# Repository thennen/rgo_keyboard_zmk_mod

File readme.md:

# R-Go split keyboard, converted to fully wireless with nice!nano + ZMK

This is a hardware and firmware mod of the commercially available R-Go split wireless keyboard. The stock electronics are replaced with a [nice!nano v2](https://nicekeyboards.com/nice-nano/) in each half, running [ZMK](https://zmk.dev/) firmware. The result is a truly wireless split, with no cable between the halves and fully programmable keys.

## Why

This replaces my [UltraErgo](https://github.com/thennen/ultraergo), which finally died after a decade or so and is no longer on the market. The R-Go isn't as nice, but it's currently the best low-profile, non-mechanical split keyboard you can buy: thin, compact and comfortable. The stock version has some annoying limitations though:

- **The halves are joined by a hardwired cable**, even on the "wireless" model. Only the connection to the PC is Bluetooth. The cable is also poorly made: a light tug pulls the outer insulation off and exposes the conductors.
- **No real remapping.** The halves of the split spacebar can't be mapped separately, and important keys like Print Screen hide behind Fn.
- **The macro column** on the far left triggers key combinations internally, and a whole key is spent on disabling it.
- **USB is power-only**, so the keyboard can't work over a cable, for example in the BIOS or boot menu.
- **A tiny 230 mAh battery**, even though the case has plenty of room for a bigger one.
- **No tenting.** It's not really "ergo" without it.

ZMK on a nice!nano fixes the electronics side: every key is programmable, both halves are wireless, and USB works for typing and flashing. For tenting, I stuck adhesive tenting stands from AliExpress on the bottom of each half.

## The stock hardware

- **Left half (control board `K900-BT LEFT V1.0`, 2023-06-25):** 100 × 24 × 1 mm with an HS6620 Bluetooth SoC (from HunterSun, now OnMicro), the kind of chip used in cheap smartwatches. Its SDK is only available under NDA, so reflashing the stock board isn't realistic. There's [a datasheet on archive.org](https://archive.org/details/hs6620d-data-sheet-v30/mode/2up) and [some reverse-engineering work](https://github.com/rbaron/HS6620D-smartwatch-reveng).
- **Right half (`K900-RIGHT V1.0`):** a passive board with only connectors, plus the 230 mAh battery (TW 382035). All of the right half's rows and columns, plus battery power, go to the left half over the 20-wire cable.
- **Key matrix:** a membrane with a flat ribbon cable (FFC) in each half. It's 1.0 mm pitch and about 21 mm wide, with a blue stiffener, and plugs into a bottom-contact ZIF connector. The left ribbon uses all 20 pins, the right one 18.

## The mod

Each half gets an adapter PCB with:
- a 20-pin, 1.0 mm FFC connector (TE 2-84952-0) for the stock membrane ribbon
- a nice!nano v2 footprint
- a 2-pin battery header, here for a 600 mAh 502040 LiPo, a big upgrade over the stock 230 mAh

<p align="center"><i>Inside, after the mod: a custom adapter PCB plugs into the stock membrane ribbon, with a nice!nano and its own 600 mAh battery on each side.</i></p>

The KiCad project, Gerbers and ready-to-order zips (`rgo_nicenano_left.zip`, `rgo_nicenano_right.zip`) are in [`rgo_nice!nano/`](rgo_nice!nano/). The PCBs reuse the stock mounting holes, and the inter-half cable is removed entirely.

> **Known PCB mistakes (current revision):**
> - The nice!nano's ground isn't connected to the battery's ground. Add a jumper wire between them.
> - On the right-hand board, the mounting hole is slightly out of place. Filing it a bit makes it fit.

Fitting notes:
- The case's inner space is about 6 mm deep and 21 mm tall in the flat part. The usable length is about 150 mm in the left half and 135 mm in the right half.
- The nice!nano fits inside easily, but it doesn't line up with the stock USB-C cutout because of the angle. The right half has no cutout at all, so expect to cut new openings.
- Socket headers are too tall for the space, even Mill-Max "super low profile" at 4 mm.

### Opening the case

Push a sharp piece of plastic, such as a plastic razor blade, into the seam. Each half has three clips on each flat side and four on the jagged side. Start with the flat sides.

The magnets tend to pop out because the glue is weak. You can glue them back in, but check the polarity so they attract instead of repel.

> **Wired vs. wireless:** The cheaper **wired** R-Go split also works as a base for this mod, since the matrix and ribbon are the same idea. But it has a hidden screw underneath the glued panels, which is quite annoying to get out.

## Firmware

The ZMK config is in [`config/boards/shields/rgo/`](config/boards/shields/rgo/), set up as a split shield (`rgo_left` / `rgo_right`) on `nice_nano_v2`. The left half is the central.

The membrane matrix (8 rows × 12 columns on the left, 8 × 10 on the right) was reverse-engineered with the `reverse_engineer_key_matrix*.py` and `capture_keys.py` scripts. They flash a test keymap that gives every matrix position a unique keycode, then record which key on the board produces which code. The resulting mapping is the `matrix-transform` in `rgo.dtsi`.

Keymap highlights (`rgo.keymap`):
- **Enter on the right half of the spacebar.** This was one of the most important reasons for the mod, since the stock firmware can't remap the two spacebar halves separately.
- **Fn layer:** Bluetooth profiles, bootloader (left: Fn+1, right: the key labeled RCtrl +7), soft-off, media keys, Print Screen, Insert and more.
- **Unicode** via [zmk-unicode](https://github.com/urob/zmk-unicode), using WinCompose.
- **Recorded macros** on the far-left column (see below).

### Recorded macros

The six keys of the far-left macro column are record-and-play slots, stored in the keyboard's flash so they survive reboots and reflashing.

- **Record:** Fn + slot key, type the sequence, then Fn + slot key again to stop and save. Use the right Fn for the top two keys, because the left Fn shares their matrix column. Keys aren't sent to the computer while recording, so the keyboard seems dead until you stop.
- **Play:** slot key alone.
- **Erase:** record an empty sequence (Fn + slot key twice). `settings_reset` also erases them.
- Up to 64 keystrokes per slot.
- Only the left half needs reflashing for changes here, since it does all the recording.

The code is in `recmac/`, a small Zephyr module that `zephyr/module.yml` at the repo root makes the build pick up. Settings like max length and playback speed are in `recmac/Kconfig`.

## Building the firmware

### Easiest: GitHub Actions (no local toolchain needed)

Every push to GitHub builds the firmware in the cloud. Three files drive it:
- `.github/workflows/build.yml` runs ZMK's reusable build workflow, pinned to v0.3.
- `build.yaml` lists which board/shield combos to build: left, right and settings_reset.
- `config/west.yml` sets which ZMK version and modules (zmk-unicode) to build against.

To get firmware:
1. Push, or on GitHub go to the Actions tab, pick the workflow and click "Run workflow".
2. Open the finished run in the Actions tab and download the `firmware` zip at the bottom.
3. Unzip, put a half into bootloader mode, and copy its `.uf2` onto the drive that appears.

To upgrade ZMK later, bump `revision` for both zmk and zmk-unicode in `config/west.yml`, and the `@v0.3` in the workflow. v0.4+ is Zephyr 4.1, where the board becomes `nice_nano//zmk` in `build.yaml`.

### tl;dr: local build and flash when the environment is already set up

Put the keyboard into bootloader mode (left half: Fn-1, right half: RCtrl-7), then in cmd.exe:
```
set PATH=%PATH%;"C:\Users\t\anaconda3\Scripts";"C:\QMK_MSYS\mingw64\bin"
subst Q: "C:\Users\t\Proton Drive\My files\github\rgo_wireless"
cd desktop\zmk\app
west build -d build/left -p -b nice_nano_v2 -- -DSHIELD=rgo_left -DZMK_CONFIG="Q:/config" -DZMK_EXTRA_MODULES="Q:/zmk-unicode;Q:/"
copy build\left\zephyr\zmk.uf2 G:\zmk.uf2
```

### Setting up a local build on Windows

You need to clone zmk. It isn't in this repo because it's 4 GB.

```
pip install west
set PATH=%PATH%;"C:\Users\t\anaconda3\Scripts";"C:\QMK_MSYS\mingw64\bin"

git clone https://github.com/zmkfirmware/zmk zmk
cd zmk
git checkout v0.3
west init -l app/
west update
west zephyr-export
```

From elevated powershell:
```
choco install cmake ninja dtc-msys2 gperf
```

```
pip install -r zephyr/scripts/requirements-base.txt
```

```
cd %HOMEPATH%
wget https://github.com/zephyrproject-rtos/sdk-ng/releases/download/v0.16.3/zephyr-sdk-0.16.3_windows-x86_64.7z
7z x zephyr-sdk-0.16.3_windows-x86_64.7z
cd zephyr-sdk-0.16.3
setup.cmd
```

To build, you need to be in the zmk/app folder:
```
cd desktop\zmk\app
```

The build command has to point to this repo's config directory, but west can't handle spaces in paths, even quoted. I use subst as a workaround on Windows:

```
subst Q: "C:\Users\t\Proton Drive\My files\github\rgo_wireless"
```

For a split build:
```
west build -d build/left -p -b nice_nano_v2 -- -DSHIELD=rgo_left -DZMK_CONFIG="Q:/config" -DZMK_EXTRA_MODULES="Q:/zmk-unicode;Q:/"
```
```
west build -d build/right -p -b nice_nano_v2 -- -DSHIELD=rgo_right -DZMK_CONFIG="Q:/config" -DZMK_EXTRA_MODULES="Q:/zmk-unicode;Q:/"
```

Put the left side into bootloader mode, then:
```
copy build\left\zephyr\zmk.uf2 E:\zmk.uf2
```

Put the right side into bootloader mode, then:
```
copy build\right\zephyr\zmk.uf2 E:\zmk.uf2
```

Sometimes you need to "reset" the keyboard by clearing the non-volatile memory. This firmware doesn't go back into bootloader mode afterwards until you reset or power-cycle it.
```
west build -d build/reset -p -b nice_nano_v2 -- -DSHIELD=settings_reset
```

ZMK overrides some config settings when it detects a split keyboard, which it seems to do from the `_left`/`_right` suffixes on the config file names. The only way to override that is a command-line option. For example, to connect the two halves to the computer separately, build with:
```
-DCONFIG_ZMK_SPLIT=n
```

`config/west.yml` and `build.yaml` are only used by the GitHub Actions build; local builds ignore them.

## Repo layout

| Path | What |
|---|---|
| `config/boards/shields/rgo/` | ZMK shield: matrix pins, matrix transform, keymap, Kconfig |
| `recmac/`, `zephyr/module.yml` | Record-and-play macro behavior (Zephyr module) |
| `rgo_nice!nano/` | KiCad project and Gerbers for the adapter PCBs |
| `nice-nano-kicad/` | nice!nano KiCad footprint (submodule) |
| `nice-nano-v2-1.snapshot.2/` | nice!nano v2 3D model, for checking fit |
| `pics/` | Photos, plus `dimensions.pptx` with case measurements |
| `reverse_engineer_key_matrix*.py`, `capture_keys.py` | Scripts used to map the membrane matrix |
| `rgo_keyboard.txt` | Raw teardown notes |
| `zmk-unicode/` | Unicode module (submodule, for local builds) |

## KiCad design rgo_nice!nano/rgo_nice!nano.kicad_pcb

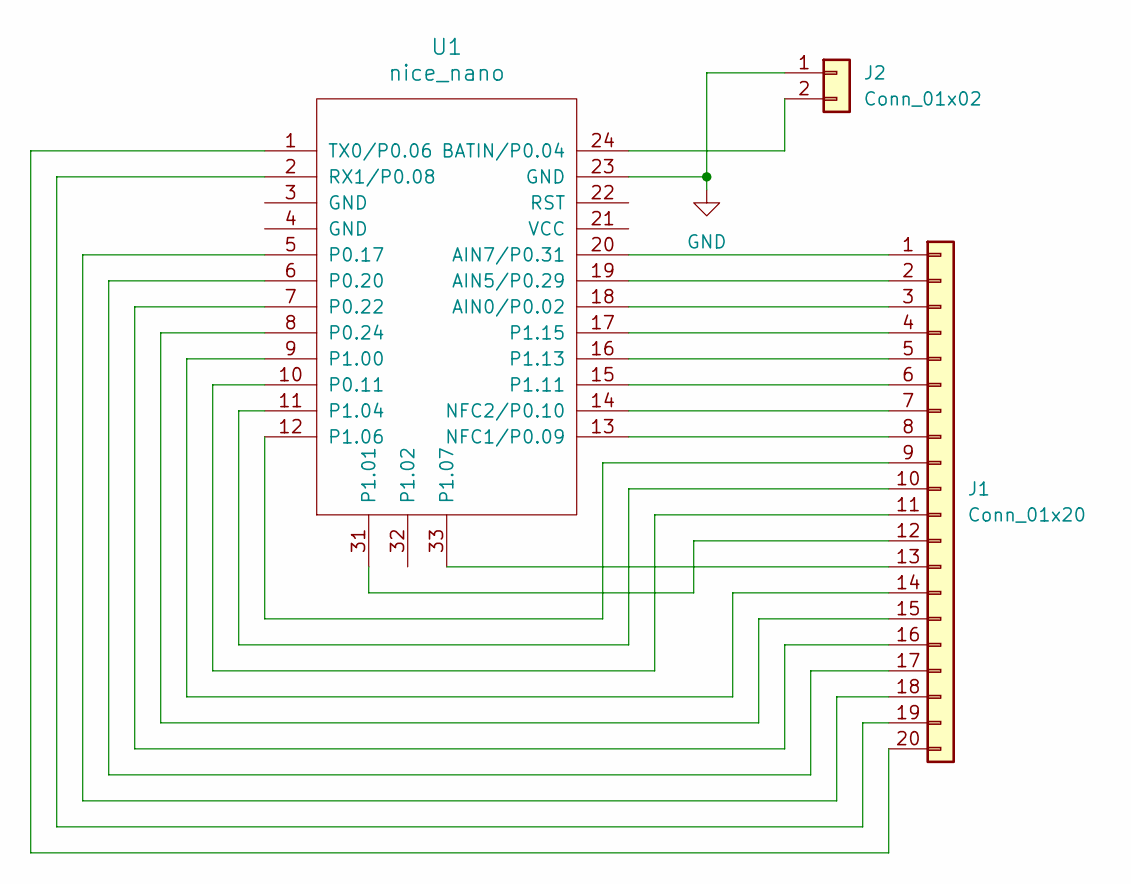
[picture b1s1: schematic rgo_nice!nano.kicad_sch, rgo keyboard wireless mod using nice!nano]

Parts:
J1: Conn_01x20; TE_2-84952-0_1x20-1MP_P1.0mm_Horizontal
J2: Conn_01x02; PinHeader_1x02_P2.54mm_Horizontal
U1: nice_nano

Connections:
GND: J2.1, U1.23 (GND)
unnamed: J1.1, U1.20 (AIN7/P0.31)
unnamed: J1.2, U1.19 (AIN5/P0.29)
unnamed: J1.3, U1.18 (AIN0/P0.02)
unnamed: J1.4, U1.17 (P1.15)
unnamed: J1.5, U1.16 (P1.13)
unnamed: J1.6, U1.15 (P1.11)
unnamed: J1.7, U1.14 (NFC2/P0.10)
unnamed: J1.8, U1.13 (NFC1/P0.09)
unnamed: J1.9, U1.12 (P1.06)
unnamed: J1.10, U1.11 (P1.04)
unnamed: J1.11, U1.10 (P0.11)
unnamed: J1.12, U1.31 (P1.01)
unnamed: J1.13, U1.33 (P1.07)
unnamed: J1.14, U1.9 (P1.00)
unnamed: J1.15, U1.8 (P0.24)
unnamed: J1.16, U1.7 (P0.22)
unnamed: J1.17, U1.6 (P0.20)
unnamed: J1.18, U1.5 (P0.17)
unnamed: J1.19, U1.2 (RX1/P0.08)
unnamed: J1.20, U1.1 (TX0/P0.06)
unnamed: J2.2, U1.24 (BATIN/P0.04)

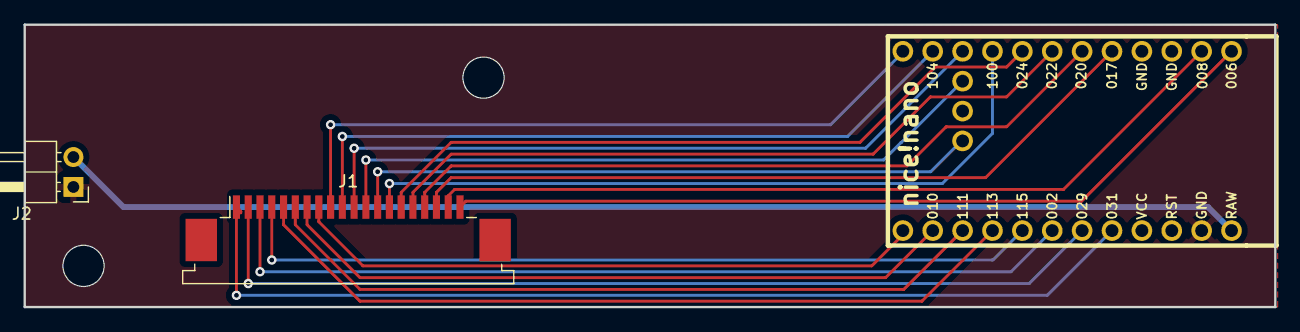
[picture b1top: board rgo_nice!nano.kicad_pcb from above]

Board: 2 copper layers, 106.3 x 24.0 mm, 3 parts (0 on the bottom side), 22 nets.

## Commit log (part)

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2025-11-16 first commit (late)
2025-11-16 tried a few things
2026-04-07 readme updates
